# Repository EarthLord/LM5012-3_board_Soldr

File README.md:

# LM5012/LM5013 regulator board made for Sodlr with KiCad

## Requirements of the board from Soldr
1. Ideas that are fun and satisfying to build
2. Not trash-bound – ideally something you'd enjoy using or keeping on your desk/shelf
3. Low production cost – target is $1–3 per unit
4. Beginner-friendly – something accessible, even if it’s your first time soldering

## Specs of the board
1. 12V to 100V input to 5V output
  1. Can be down to 6V input if voltage divider for under-voltage lockout is tweaked
  2. 5V output can change also if feedback voltage divider is changed
2. 2.5A maximum output with LM5012 and 3.5A maximum output with LM5013
3. Sub 100uA current drawn at no load
4. BoM and PCB would come to around 2 to 3 USD depending on the chip used and quantity. 

### Soldering experience
The design is made such that different component sizes and soldering gun heat levels are utilized.

1. Both through hole and surface mount components
2. All surface mount components are with larger leads for hand soldering
3. Size varies from a large inductor to 0402 capacitors and resistors for surface mount components
4. Also experience of soldering an exposed pad from the back side for the regulator

## Documentation
The design is documented in the [schematic](output/schematic.pdf). The gerber files are in the gerber folder. The renders of the board are below.

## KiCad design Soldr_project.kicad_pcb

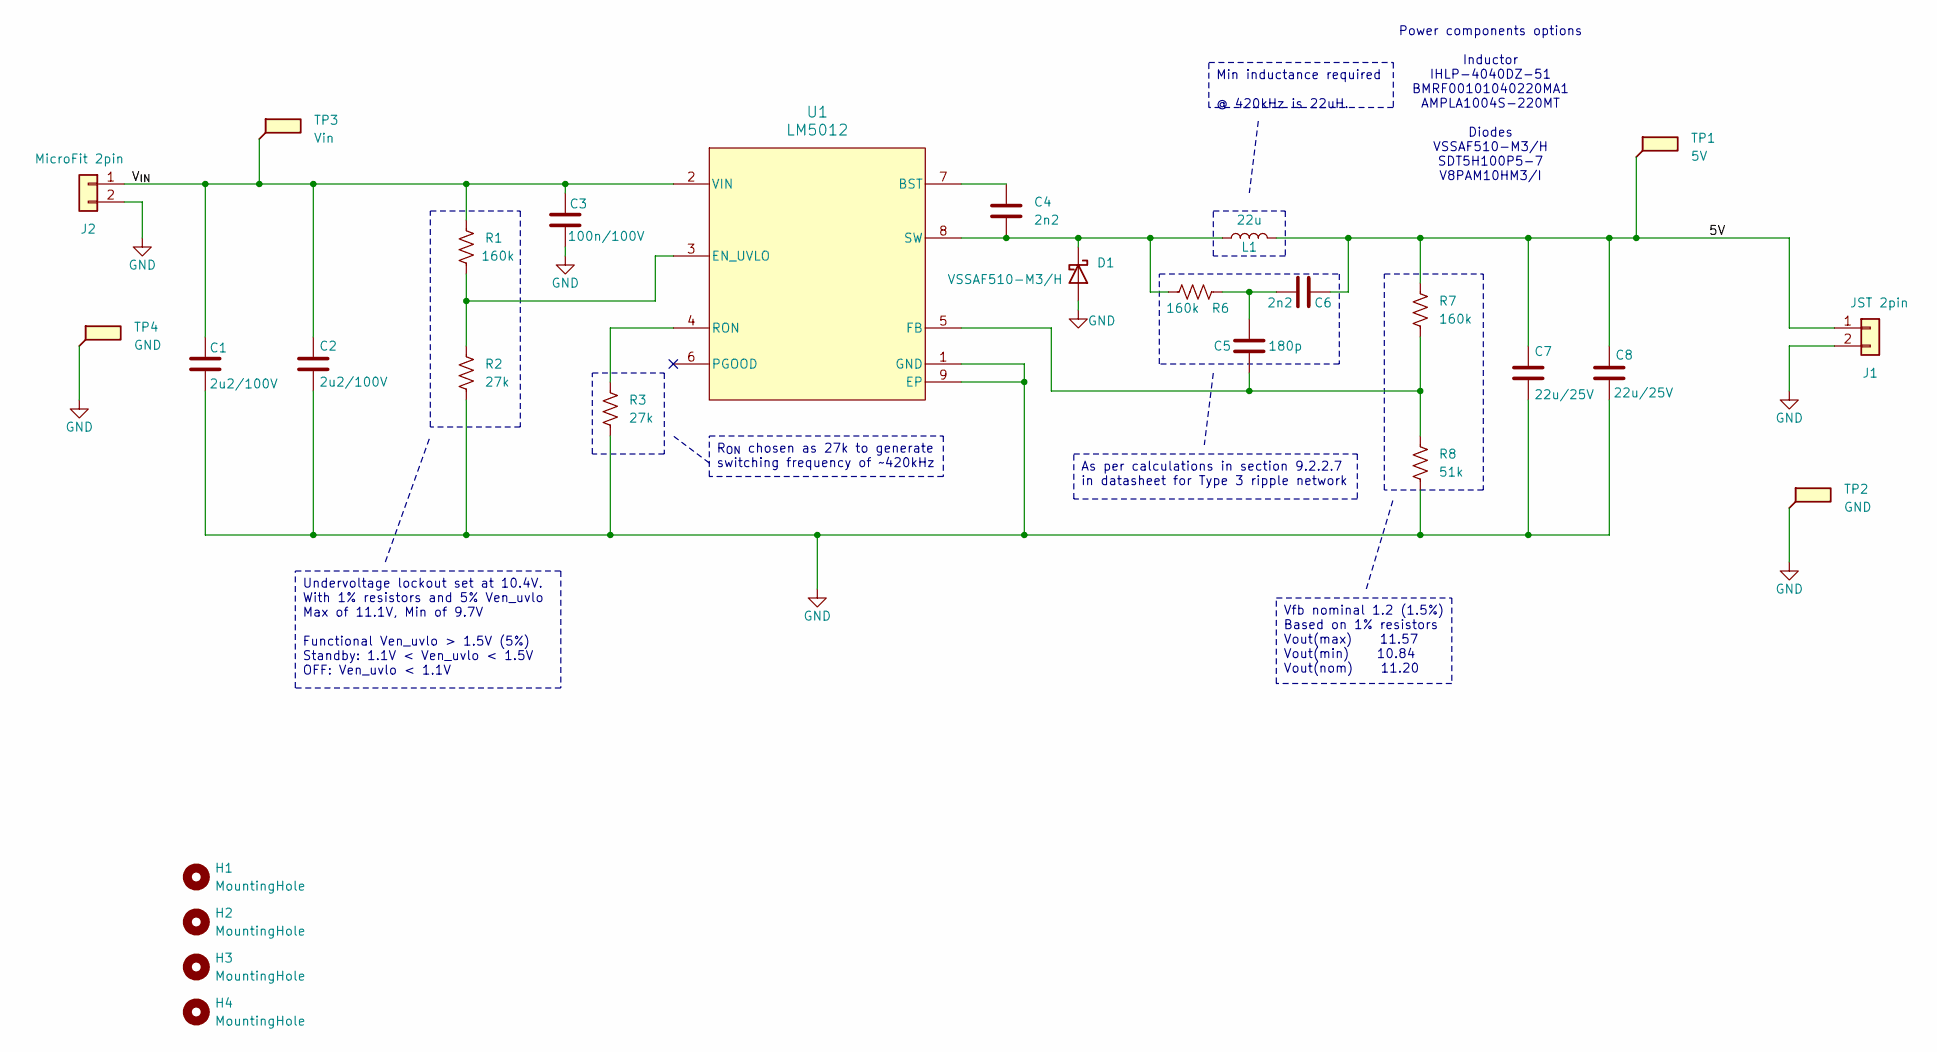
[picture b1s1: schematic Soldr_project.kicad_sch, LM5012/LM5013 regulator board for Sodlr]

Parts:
C1, C2: 2u2/100V; C_1210_3225Metric_Pad1.33x2.70mm_HandSolder
C3: 100n/100V; C_0603_1608Metric_Pad1.08x0.95mm_HandSolder
C4, C6: 2n2; C_0402_1005Metric_Pad0.74x0.62mm_HandSolder
C5: 180p; C_0402_1005Metric_Pad0.74x0.62mm_HandSolder
C7, C8: 22u/25V; C_1206_3216Metric_Pad1.33x1.80mm_HandSolder
D1: VSSAF510-M3/H; D_SMA_Handsoldering
H1, H2, H3, H4: MountingHole; MountingHole_2.7mm_M2.5
J1: JST 2pin; JST_EH_S2B-EH_1x02_P2.50mm_Horizontal
J2: MicroFit 2pin; Molex_Micro-Fit_3.0_43045-0200_2x01_P3.00mm_Horizontal
L1: 22u; L_Chilisin_BMRF00101040
R1, R6, R7: 160k; R_0402_1005Metric_Pad0.72x0.64mm_HandSolder
R2, R3: 27k; R_0402_1005Metric_Pad0.72x0.64mm_HandSolder
R8: 51k; R_0402_1005Metric_Pad0.72x0.64mm_HandSolder
TP1: 5V; TestPoint_THTPad_D2.5mm_Drill1.2mm
TP2, TP4: GND; TestPoint_THTPad_D2.5mm_Drill1.2mm
TP3: Vin; TestPoint_THTPad_D2.5mm_Drill1.2mm
U1: LM5012; SOIC-8-1EP_3.9x4.9mm_P1.27mm_EP2.29x3mm_ThermalVias

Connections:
/5V: C6.2, C7.1, C8.1, J1.1, L1.2, R7.1, TP1.1
/V_{IN}: C1.1, C2.1, C3.1, J2.1, R1.1, TP3.1, U1.2 (VIN)
GND: C1.2, C2.2, C3.2, C7.2, C8.2, D1.2 (A), J1.2, J2.2, R2.2, R3.2, R8.2, TP2.1, TP4.1, U1.1 (GND), U1.9 (EP)
unnamed: C5.2, C6.1, R6.2
unnamed: C4.2, D1.1 (K), L1.1, R6.1, U1.8 (SW)
unnamed: C4.1, U1.7 (BST)
unnamed: R1.2, R2.1, U1.3 (EN_UVLO)
unnamed: C5.1, R7.2, R8.1, U1.5 (FB)
unnamed: R3.1, U1.4 (RON)

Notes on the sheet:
Power components options Inductor IHLP-4040DZ-51 BMRF00101040220MA1 AMPLA1004S-220MT Diodes VSSAF510-M3/H SDT5H100P5-7 V8PAM10HM3/I
Min inductance required @ 420kHz is 22uH.
As per calculations in section 9.2.2.7 in datasheet for Type 3 ripple network
Vfb nominal 1.2 (1.5%) Based on 1% resistors Vout(max) 11.57 Vout(min) 10.84 Vout(nom) 11.20
Undervoltage lockout set at 10.4V. With 1% resistors and 5% Ven_uvlo Max of 11.1V, Min of 9.7V Functional Ven_uvlo > 1.5V (5%) Standby: 1.1V < Ven_uvlo < 1.5V OFF: Ven_uvlo < 1.1V
R_{ON} chosen as 27k to generate switching frequency of ~420kHz

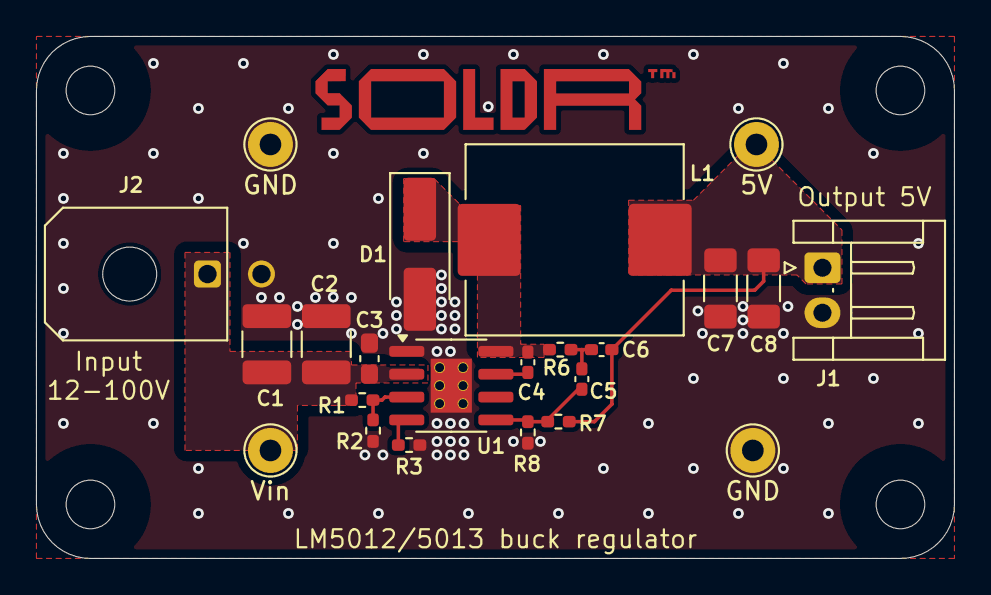
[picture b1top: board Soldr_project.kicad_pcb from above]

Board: 2 copper layers, 51.0 x 29.0 mm, 27 parts (0 on the bottom side), 9 nets.

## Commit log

2025-04-05 Update README.md with requirements, specs and soldering experience
2025-04-05 Add the KiCad PCB design for the board
2025-04-05 Update README.md with link to schematic and pictures of the board
2025-04-05 Update README.md with point on BoM
